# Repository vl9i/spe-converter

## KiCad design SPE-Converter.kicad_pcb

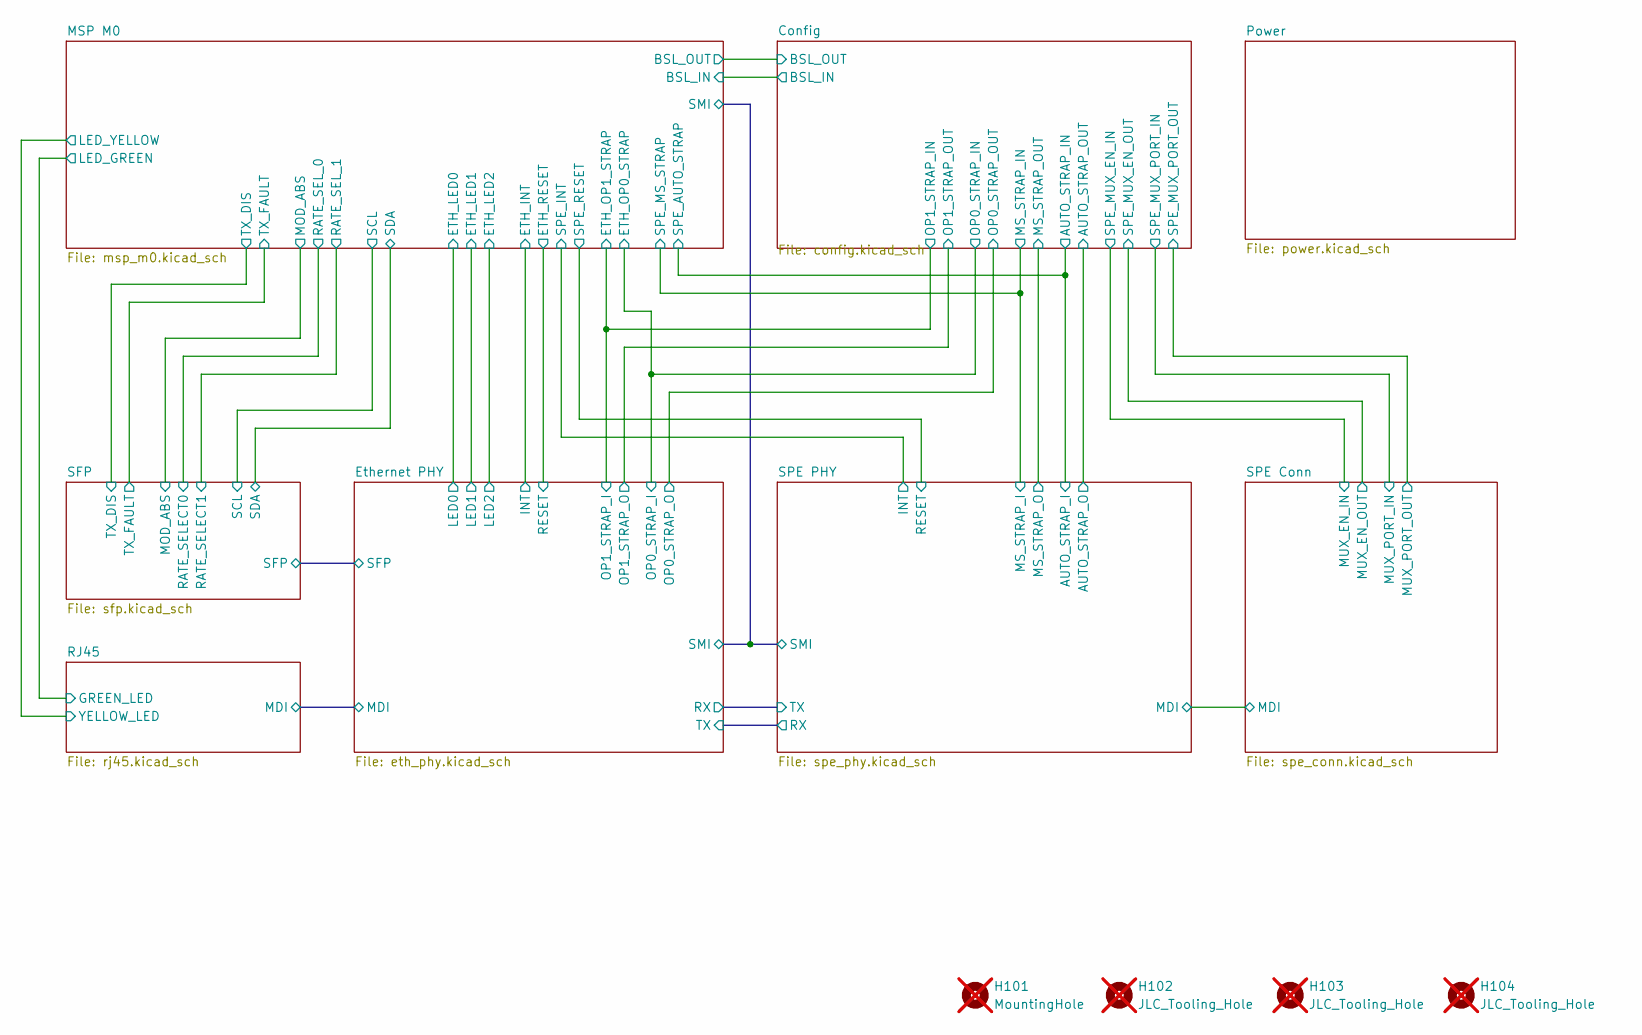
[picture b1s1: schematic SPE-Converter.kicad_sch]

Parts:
H101: MountingHole; MountingHole_2.7mm_M2.5; not fitted
H102, H103, H104: JLC_Tooling_Hole; not fitted

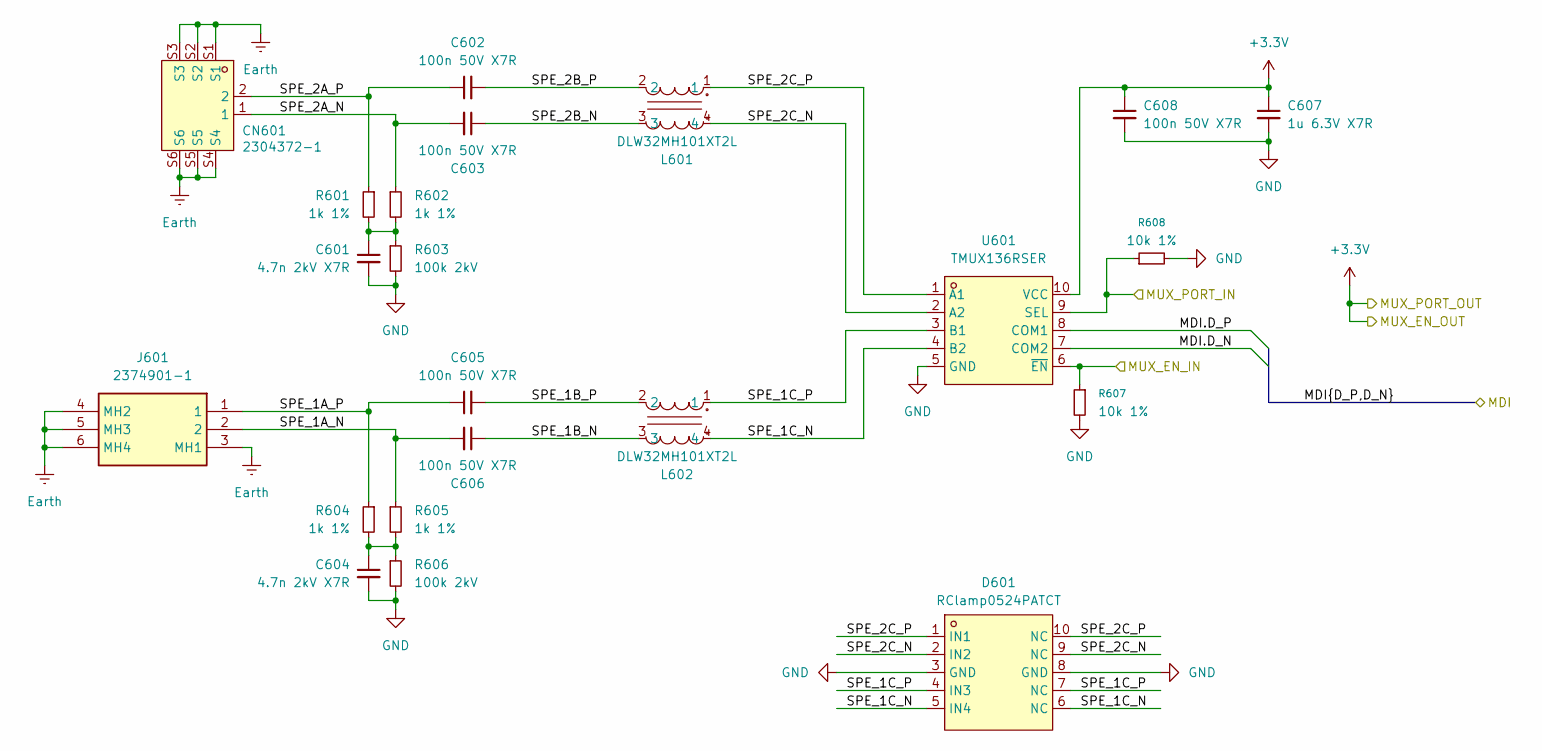
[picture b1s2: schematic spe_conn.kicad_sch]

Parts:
C601, C604: 4.7n 2kV X7R; C_1206_3216Metric
C602, C603, C605, C606, C608: 100n 50V X7R; C_0402_1005Metric
C607: 1u 6.3V X7R; C_0402_1005Metric
CN601: 2304372-1; CONN-TH_2304372-1; MPN 2304372-1; LCSC Part C5157090
D601: RClamp0524PATCT; SLP2510P8_L2.5-W1.0-P0.50-BL; MPN RClAMP0524PATCT; LCSC Part C40960
J601: 2374901-1; 23749011; Mouser Part Number 571-2374901-1
L601, L602: DLW32MH101XT2L; FILTER-SMD_4P-L3.2-W2.5-BL_DLW32SH510XK2L; LCSC Part C2935101
R601, R602, R604, R605: 1k 1%; R_0805_2012Metric
R603, R606: 100k 2kV; R_1206_3216Metric
R607, R608: 10k 1%; R_0402_1005Metric
U601: TMUX136RSER; UQFN-10_L2.0-W1.5-P0.50-TL; MPN TMUX136RSER; LCSC Part C2673272

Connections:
+3.3V: C607.1, C608.1, U601.10 (VCC); also elsewhere on the board
/Config/SPE_MUX_EN_IN: R607.1, U601.6 (~EN); also elsewhere on the board
/Config/SPE_MUX_PORT_IN: R608.1, U601.9 (SEL); also elsewhere on the board
/SPE Conn/MDI.D_N: U601.7 (COM2); also elsewhere on the board
/SPE Conn/MDI.D_P: U601.8 (COM1); also elsewhere on the board
/SPE Conn/SPE_1A_N: C606.2, J601.2, R605.1
/SPE Conn/SPE_1A_P: C605.1, J601.1, R604.1
/SPE Conn/SPE_1B_N: C606.1, L602.3
/SPE Conn/SPE_1B_P: C605.2, L602.2
/SPE Conn/SPE_1C_N: D601.5 (IN4), D601.6 (NC), L602.4, U601.4 (B2)
/SPE Conn/SPE_1C_P: D601.4 (IN3), D601.7 (NC), L602.1, U601.3 (B1)
/SPE Conn/SPE_2A_N: C603.2, CN601.1, R602.1
/SPE Conn/SPE_2A_P: C602.1, CN601.2, R601.1
/SPE Conn/SPE_2B_N: C603.1, L601.3
/SPE Conn/SPE_2B_P: C602.2, L601.2
/SPE Conn/SPE_2C_N: D601.2 (IN2), D601.9 (NC), L601.4, U601.2 (A2)
/SPE Conn/SPE_2C_P: D601.1 (IN1), D601.10 (NC), L601.1, U601.1 (A1)
Earth: CN601.S1, CN601.S2, CN601.S3, CN601.S4, CN601.S5, CN601.S6, J601.3 (MH1), J601.4 (MH2), J601.5 (MH3), J601.6 (MH4); also elsewhere on the board
GND: C601.2, C604.2, C607.2, C608.2, D601.3 (GND), D601.8 (GND), R603.2, R606.2, R607.2, R608.2, U601.5 (GND); also elsewhere on the board
unnamed: C601.1, R601.2, R602.2, R603.1
unnamed: C604.1, R604.2, R605.2, R606.1

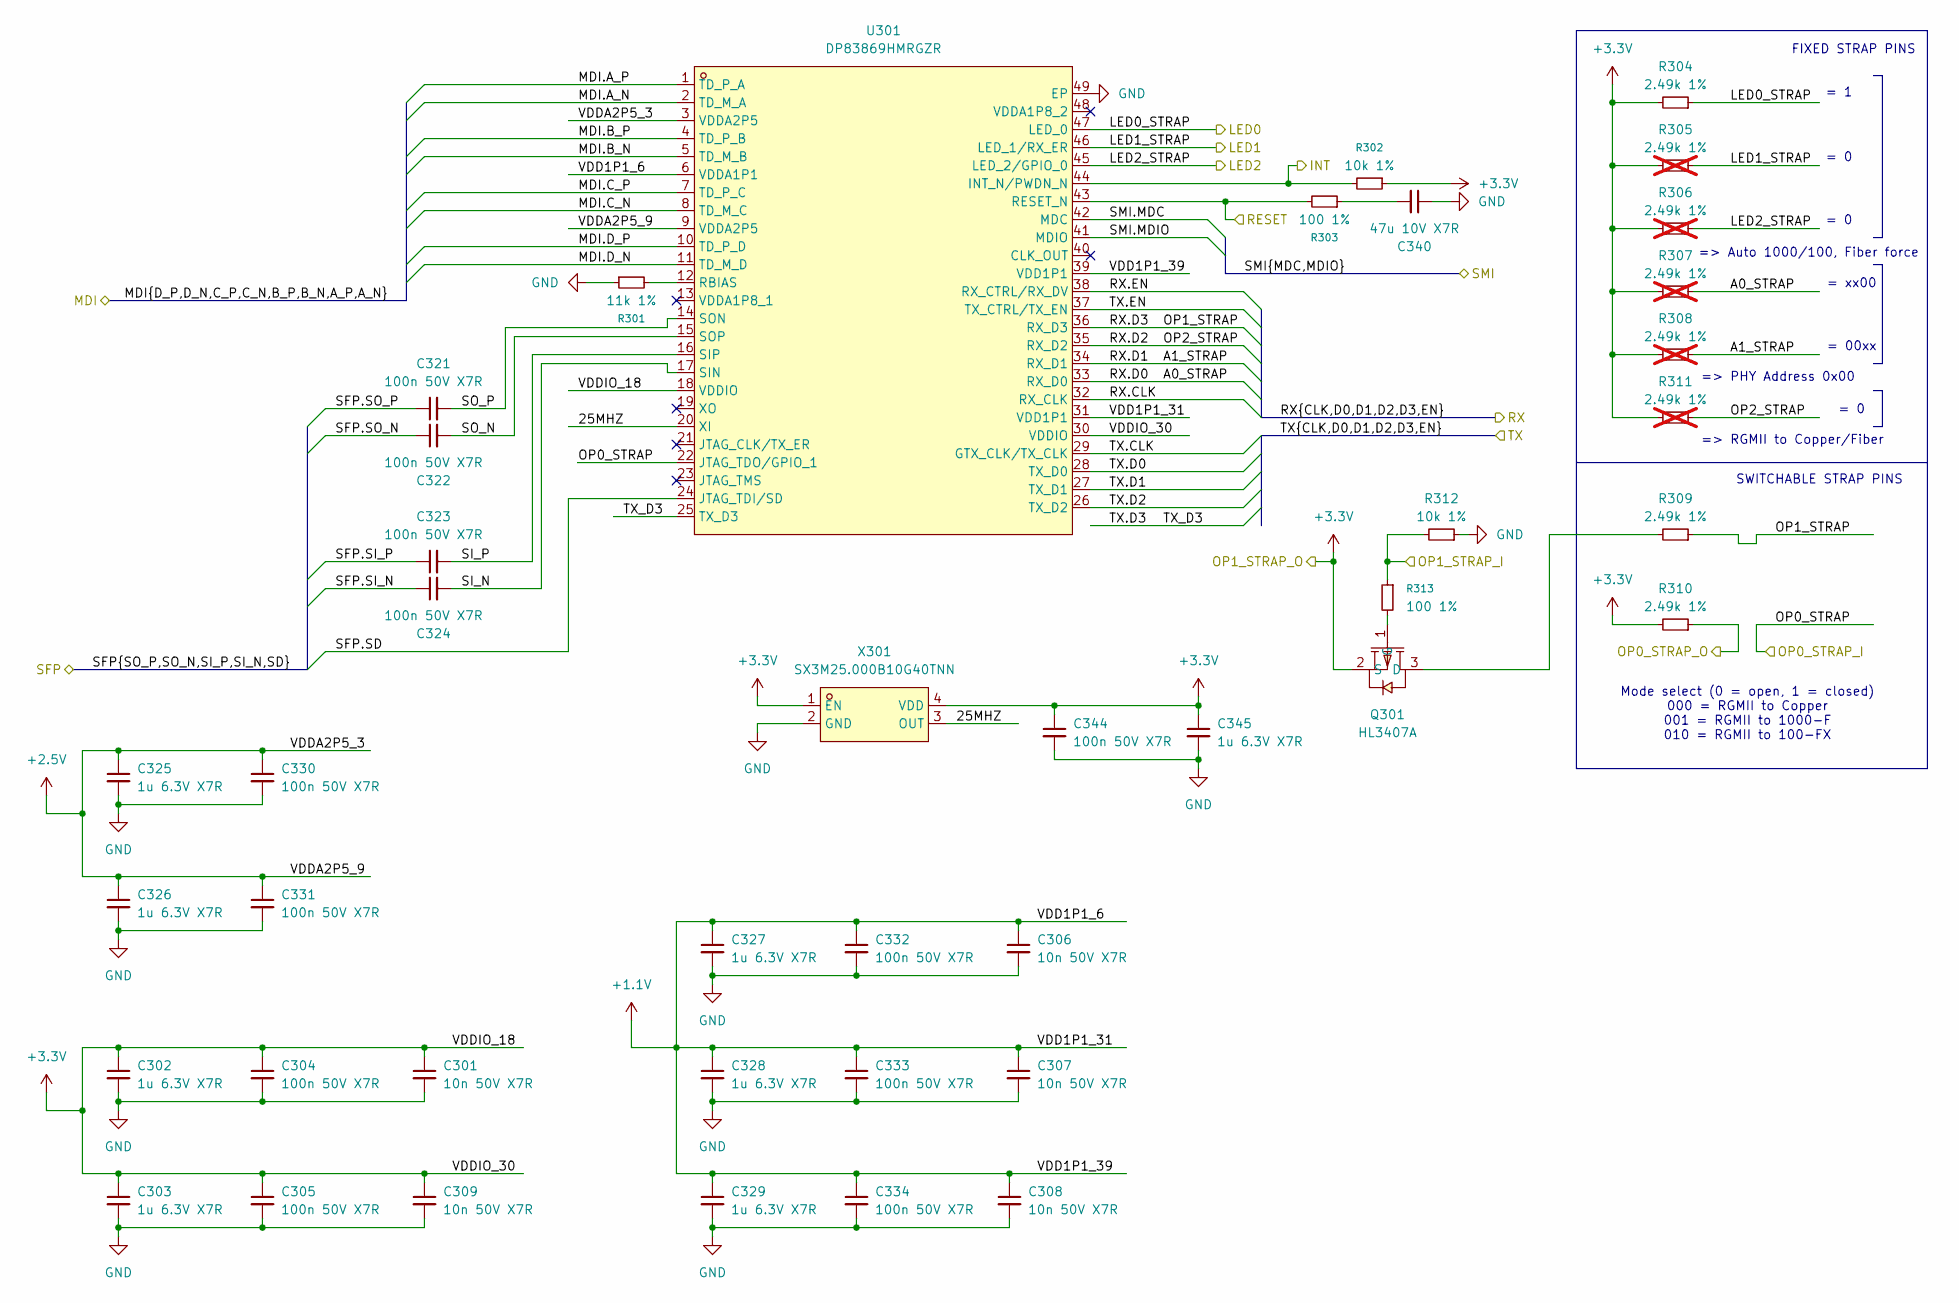
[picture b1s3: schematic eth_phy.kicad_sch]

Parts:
C301, C306, C307, C308, C309: 10n 50V X7R; C_0402_1005Metric
C302, C303, C325, C326, C327, C328, C329, C345: 1u 6.3V X7R; C_0402_1005Metric
C304, C305, C321, C322, C323, C324, C330, C331, C332, C333, C334, C344: 100n 50V X7R; C_0402_1005Metric
C340: 47u 10V X7R; C_1206_3216Metric
Q301: HL3407A; SOT-23-3_L2.9-W1.3-P1.90-LS2.4-BL-1; MPN HL3407A; LCSC Part C28646269
R301: 11k 1%; R_0402_1005Metric
R302, R312: 10k 1%; R_0402_1005Metric
R303, R313: 100 1%; R_0402_1005Metric
R304, R309, R310: 2.49k 1%; R_0402_1005Metric
R305, R306, R307, R308, R311: 2.49k 1%; R_0402_1005Metric; not fitted
U301: DP83869HMRGZR; VQFN-48_L7.0-W7.0-P0.50-TL-EP; LCSC Part C2672408
X301: SX3M25.000B10G40TNN; OSC-SMD_4P-L3.2-W2.5-BL-1; MPN SX3M25.000B10G40TNN; LCSC Part C5452698

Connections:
+1.1V: C306.1, C307.1, C308.1, C327.1, C328.1, C329.1, C332.1, C333.1, C334.1, U301.6 (VDDA1P1), U301.31 (VDD1P1), U301.39 (VDD1P1); also elsewhere on the board
+2.5V: C325.1, C326.1, C330.1, C331.1, U301.3 (VDDA2P5), U301.9 (VDDA2P5); also elsewhere on the board
+3.3V: C301.1, C302.1, C303.1, C304.1, C305.1, C309.1, C344.1, C345.1, Q301.2 (S), R302.1, R304.2, R305.2, R306.2, R307.2, R308.2, R310.2, R311.2, U301.18 (VDDIO), U301.30 (VDDIO), X301.1 (EN), X301.4 (VDD); also elsewhere on the board
/Config/OP0_STRAP_OUT: R310.1; also elsewhere on the board
/Config/OP1_STRAP_IN: R312.2, R313.1; also elsewhere on the board
/Ethernet PHY/25MHZ: U301.20 (XI), X301.3 (OUT)
/Ethernet PHY/INT: R302.2, U301.44 (INT_N/PWDN_N); also elsewhere on the board
/Ethernet PHY/LED0_STRAP: R304.1, U301.47 (LED_0); also elsewhere on the board
/Ethernet PHY/LED1_STRAP: R305.1, U301.46 (LED_1/RX_ER); also elsewhere on the board
/Ethernet PHY/LED2_STRAP: R306.1, U301.45 (LED_2/GPIO_0); also elsewhere on the board
/Ethernet PHY/MDI.A_N: U301.2 (TD_M_A); also elsewhere on the board
/Ethernet PHY/MDI.A_P: U301.1 (TD_P_A); also elsewhere on the board
/Ethernet PHY/MDI.B_N: U301.5 (TD_M_B); also elsewhere on the board
/Ethernet PHY/MDI.B_P: U301.4 (TD_P_B); also elsewhere on the board
/Ethernet PHY/MDI.C_N: U301.8 (TD_M_C); also elsewhere on the board
/Ethernet PHY/MDI.C_P: U301.7 (TD_P_C); also elsewhere on the board
/Ethernet PHY/MDI.D_N: U301.11 (TD_M_D); also elsewhere on the board
/Ethernet PHY/MDI.D_P: U301.10 (TD_P_D); also elsewhere on the board
/Ethernet PHY/OP0_STRAP: U301.22 (JTAG_TDO/GPIO_1); also elsewhere on the board
/Ethernet PHY/RESET: R303.2, U301.43 (RESET_N); also elsewhere on the board
/Ethernet PHY/RX.CLK: U301.32 (RX_CLK); also elsewhere on the board
/Ethernet PHY/RX.D0: R307.1, U301.33 (RX_D0); also elsewhere on the board
/Ethernet PHY/RX.D1: R308.1, U301.34 (RX_D1); also elsewhere on the board
/Ethernet PHY/RX.D2: R311.1, U301.35 (RX_D2); also elsewhere on the board
/Ethernet PHY/RX.D3: R309.1, U301.36 (RX_D3); also elsewhere on the board
/Ethernet PHY/RX.EN: U301.38 (RX_CTRL/RX_DV); also elsewhere on the board
/Ethernet PHY/SFP.SD: U301.24 (JTAG_TDI/SD); also elsewhere on the board
/Ethernet PHY/SFP.SI_N: C324.1; also elsewhere on the board
/Ethernet PHY/SFP.SI_P: C323.1; also elsewhere on the board
/Ethernet PHY/SFP.SO_N: C322.1; also elsewhere on the board
/Ethernet PHY/SFP.SO_P: C321.1; also elsewhere on the board
/Ethernet PHY/SI_N: C324.2, U301.17 (SIN)
/Ethernet PHY/SI_P: C323.2, U301.16 (SIP)
/Ethernet PHY/SMI.MDC: U301.42 (MDC); also elsewhere on the board
/Ethernet PHY/SMI.MDIO: U301.41 (MDIO); also elsewhere on the board
/Ethernet PHY/SO_N: C322.2, U301.15 (SOP)
/Ethernet PHY/SO_P: C321.2, U301.14 (SON)
/Ethernet PHY/TX.CLK: U301.29 (GTX_CLK/TX_CLK); also elsewhere on the board
/Ethernet PHY/TX.D0: U301.28 (TX_D0); also elsewhere on the board
/Ethernet PHY/TX.D1: U301.27 (TX_D1); also elsewhere on the board
/Ethernet PHY/TX.D2: U301.26 (TX_D2); also elsewhere on the board
/Ethernet PHY/TX.D3: U301.25 (TX_D3); also elsewhere on the board
/Ethernet PHY/TX.EN: U301.37 (TX_CTRL/TX_EN); also elsewhere on the board
GND: C301.2, C302.2, C303.2, C304.2, C305.2, C306.2, C307.2, C308.2, C309.2, C325.2, C326.2, C327.2, C328.2, C329.2, C330.2, C331.2, C332.2, C333.2, C334.2, C340.1, C344.2, C345.2, R301.1, R312.1, U301.49 (EP), X301.2 (GND); also elsewhere on the board
unnamed: C340.2, R303.1
unnamed: Q301.3 (D), R309.2
unnamed: Q301.1 (G), R313.2
unnamed: R301.2, U301.12 (RBIAS)

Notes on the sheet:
Mode select (0 = open, 1 = closed) 000 = RGMII to Copper 001 = RGMII to 1000-F 010 = RGMII to 100-FX
=> RGMII to Copper/Fiber
= 0
=> Auto 1000/100, Fiber force
= xx00
FIXED STRAP PINS
= 0
= 00xx
=> PHY Address 0x00
SWITCHABLE STRAP PINS
= 1

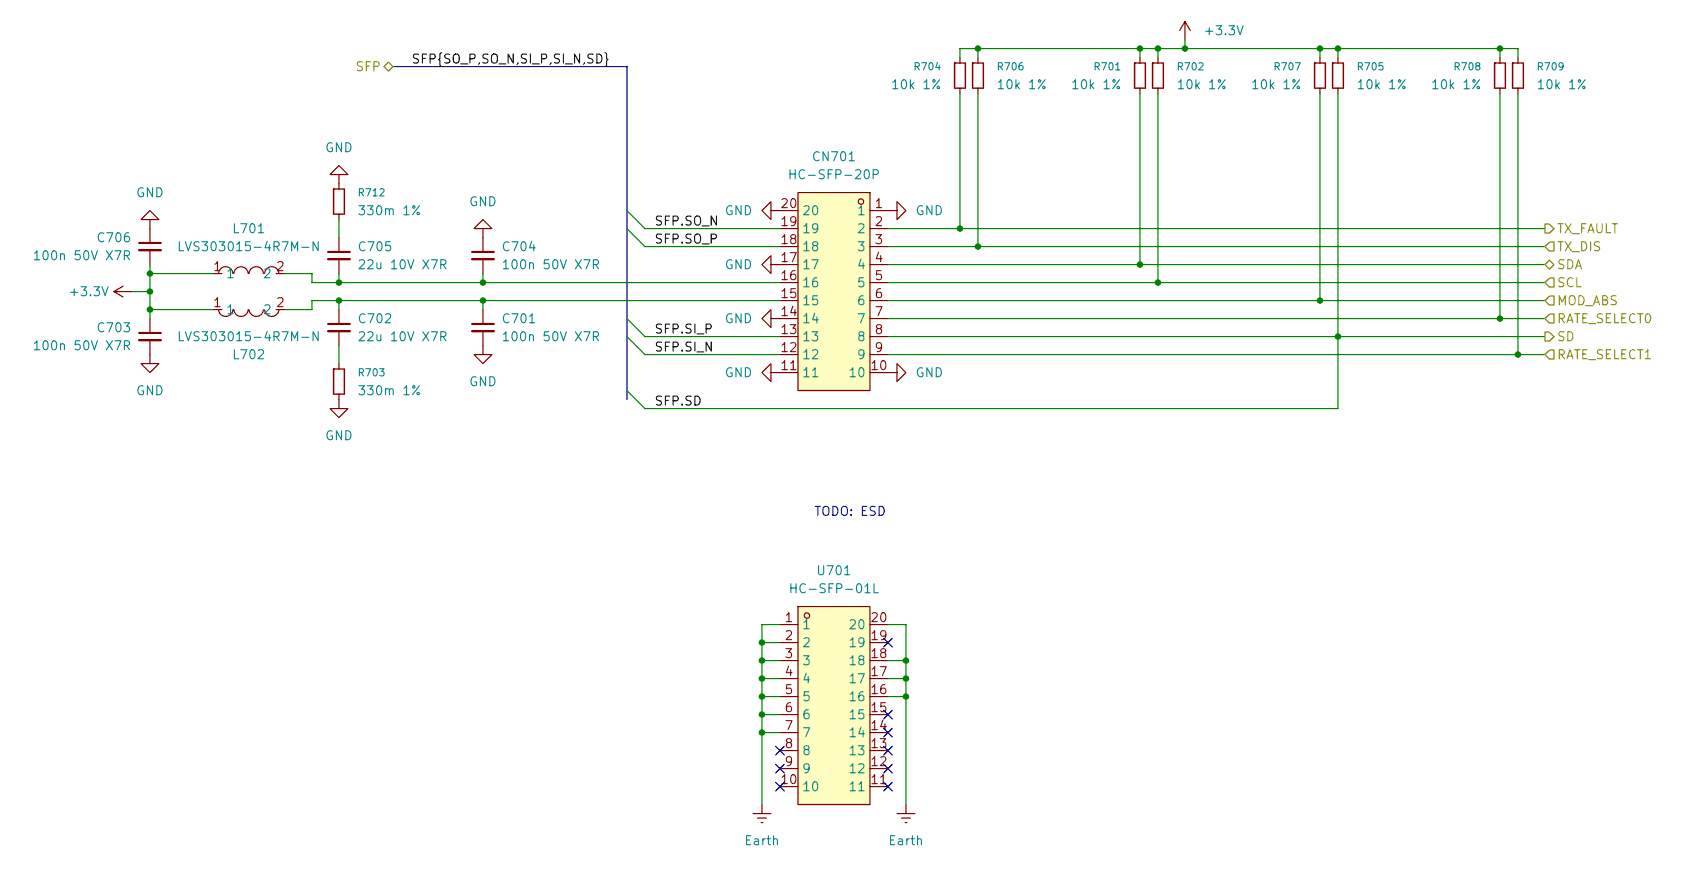
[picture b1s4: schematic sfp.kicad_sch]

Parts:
C701, C703, C704, C706: 100n 50V X7R; C_0402_1005Metric
C702, C705: 22u 10V X7R; C_0805_2012Metric
CN701: HC-SFP-20P; CONN-SMD_20P-P0.80_HCTL_HC-SFP-20P; MPN HC-SFP-20P; LCSC Part C2897291
L701, L702: LVS303015-4R7M-N; IND-SMD_L3.0-W3.0_NR3010; MPN LVS303015-4R7M-N; LCSC Part C280523
R701, R702, R704, R705, R706, R707, R708, R709: 10k 1%; R_0402_1005Metric
R703, R712: 330m 1%; R_0402_1005Metric
U701: HC-SFP-01L; TH_HC-SFP-01L; MPN HC-SFP-01L; LCSC Part C2897292

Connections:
+3.3V: C703.1, C706.2, L701.1, L702.1, R701.1, R702.1, R704.1, R705.1, R706.1, R707.1, R708.1, R709.1; also elsewhere on the board
/Ethernet PHY/SFP.SD: CN701.8, R705.2; also elsewhere on the board
/Ethernet PHY/SFP.SI_N: CN701.12; also elsewhere on the board
/Ethernet PHY/SFP.SI_P: CN701.13; also elsewhere on the board
/Ethernet PHY/SFP.SO_N: CN701.19; also elsewhere on the board
/Ethernet PHY/SFP.SO_P: CN701.18; also elsewhere on the board
/MSP M0/MOD_ABS: CN701.6, R707.2; also elsewhere on the board
/MSP M0/RATE_SEL_0: CN701.7, R708.2; also elsewhere on the board
/MSP M0/RATE_SEL_1: CN701.9, R709.2; also elsewhere on the board
/MSP M0/SCL: CN701.5, R702.2; also elsewhere on the board
/MSP M0/SDA: CN701.4, R701.2; also elsewhere on the board
/MSP M0/TX_DIS: CN701.3, R706.2; also elsewhere on the board
/MSP M0/TX_FAULT: CN701.2, R704.2; also elsewhere on the board
Earth: U701.1, U701.2, U701.3, U701.4, U701.5, U701.6, U701.7, U701.16, U701.17, U701.18, U701.20; also elsewhere on the board
GND: C701.2, C703.2, C704.1, C706.1, CN701.1, CN701.10, CN701.11, CN701.14, CN701.17, CN701.20, R703.2, R712.1; also elsewhere on the board
unnamed: C701.1, C702.1, CN701.15, L702.2
unnamed: C702.2, R703.1
unnamed: C704.2, C705.2, CN701.16, L701.2
unnamed: C705.1, R712.2

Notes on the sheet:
TODO: ESD

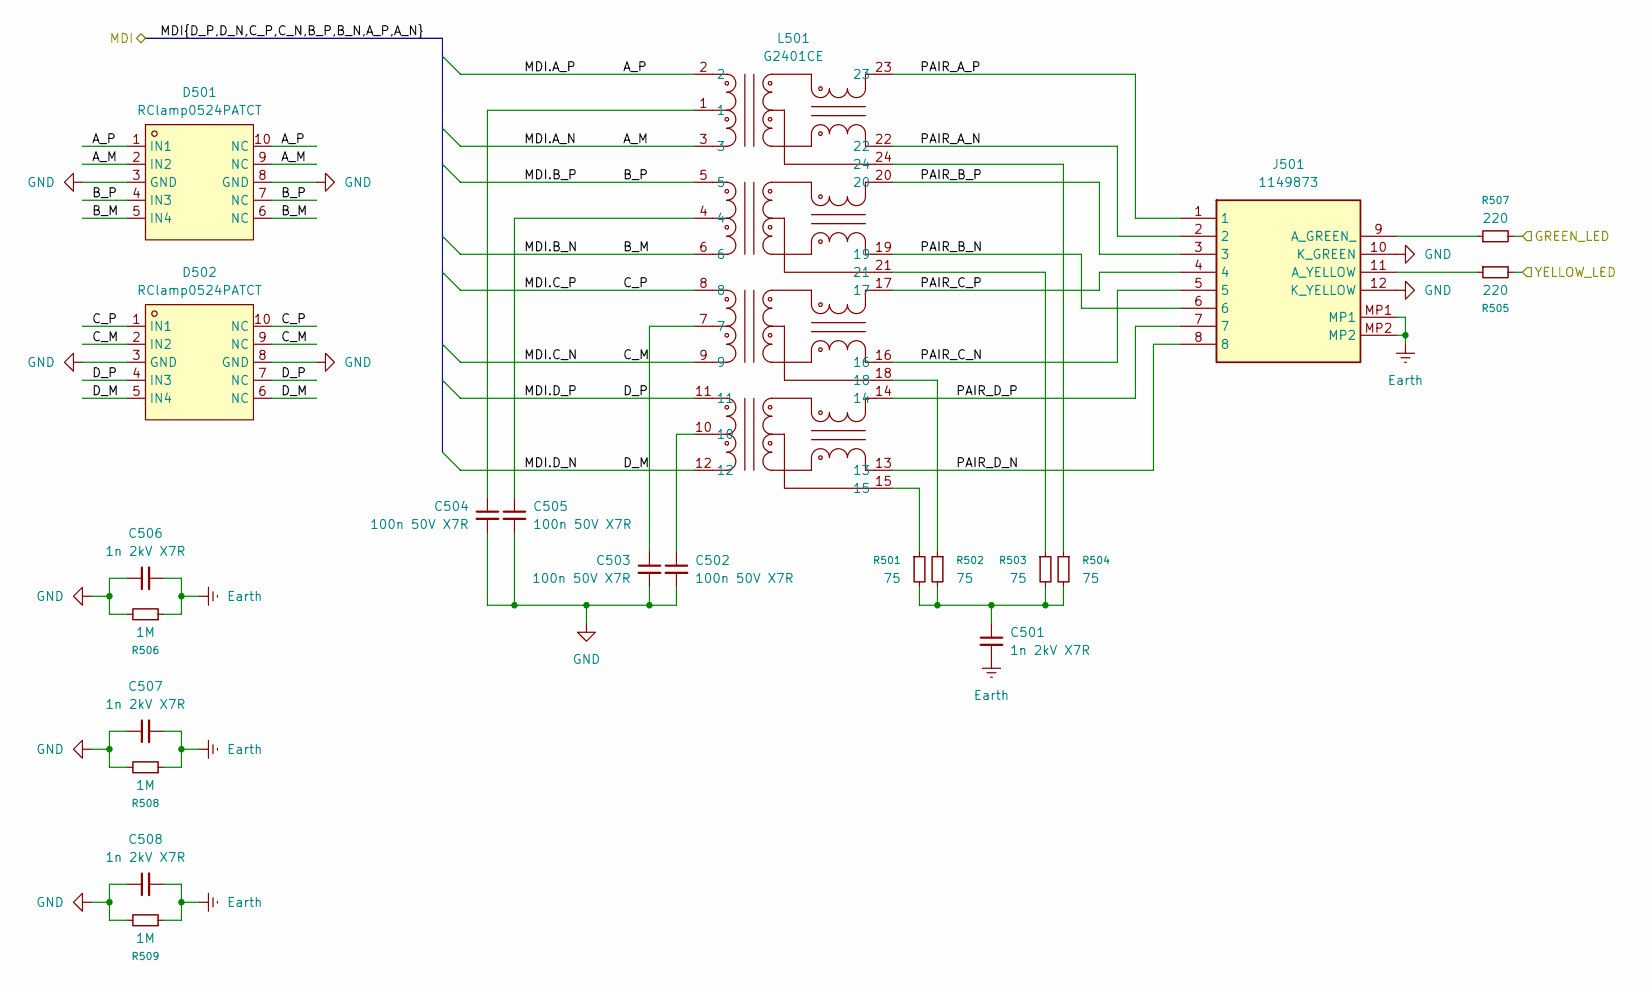
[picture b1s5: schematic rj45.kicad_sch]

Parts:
C501, C506, C507, C508: 1n 2kV X7R; C_1210_3225Metric
C502, C503, C504, C505: 100n 50V X7R; C_0402_1005Metric
D501, D502: RClamp0524PATCT; SLP2510P8_L2.5-W1.0-P0.50-BL; MPN RClAMP0524PATCT; LCSC Part C40960
J501: 1149873; Manufacturer_Part_Number 1149873; Mouser Part Number 651-1149873
L501: G2401CE; SMD-24_L15.1-W7.1-P1.00-LS10.0-BL; MPN G2401CE; LCSC Part C2904710
R501, R502, R503, R504: 75; R_0402_1005Metric
R505, R507: 220; R_0402_1005Metric
R506, R508, R509: 1M; R_1206_3216Metric

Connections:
/Ethernet PHY/MDI.A_N: D501.2 (IN2), D501.9 (NC), L501.3; also elsewhere on the board
/Ethernet PHY/MDI.A_P: D501.1 (IN1), D501.10 (NC), L501.2; also elsewhere on the board
/Ethernet PHY/MDI.B_N: D501.5 (IN4), D501.6 (NC), L501.6; also elsewhere on the board
/Ethernet PHY/MDI.B_P: D501.4 (IN3), D501.7 (NC), L501.5; also elsewhere on the board
/Ethernet PHY/MDI.C_N: D502.2 (IN2), D502.9 (NC), L501.9; also elsewhere on the board
/Ethernet PHY/MDI.C_P: D502.1 (IN1), D502.10 (NC), L501.8; also elsewhere on the board
/Ethernet PHY/MDI.D_N: D502.5 (IN4), D502.6 (NC), L501.12; also elsewhere on the board
/Ethernet PHY/MDI.D_P: D502.4 (IN3), D502.7 (NC), L501.11; also elsewhere on the board
/MSP M0/LED_GREEN: R507.2; also elsewhere on the board
/MSP M0/LED_YELLOW: R505.2; also elsewhere on the board
/RJ45/PAIR_A_N: J501.2, L501.22
/RJ45/PAIR_A_P: J501.1, L501.23
/RJ45/PAIR_B_N: J501.6, L501.19
/RJ45/PAIR_B_P: J501.3, L501.20
/RJ45/PAIR_C_N: J501.5, L501.16
/RJ45/PAIR_C_P: J501.4, L501.17
/RJ45/PAIR_D_N: J501.8, L501.13
/RJ45/PAIR_D_P: J501.7, L501.14
Earth: C501.2, C506.2, C507.2, C508.2, J501.MP1, J501.MP2, R506.1, R508.1, R509.1; also elsewhere on the board
GND: C502.2, C503.2, C504.2, C505.2, C506.1, C507.1, C508.1, D501.3 (GND), D501.8 (GND), D502.3 (GND), D502.8 (GND), J501.10 (K_GREEN), J501.12 (K_YELLOW), R506.2, R508.2, R509.2; also elsewhere on the board
unnamed: C501.1, R501.2, R502.2, R503.2, R504.2
unnamed: C502.1, L501.10
unnamed: C503.1, L501.7
unnamed: C504.1, L501.1
unnamed: C505.1, L501.4
unnamed: J501.9 (A_GREEN_), R507.1
unnamed: J501.11 (A_YELLOW), R505.1
unnamed: L501.15, R501.1
unnamed: L501.18, R502.1
unnamed: L501.21, R503.1
unnamed: L501.24, R504.1

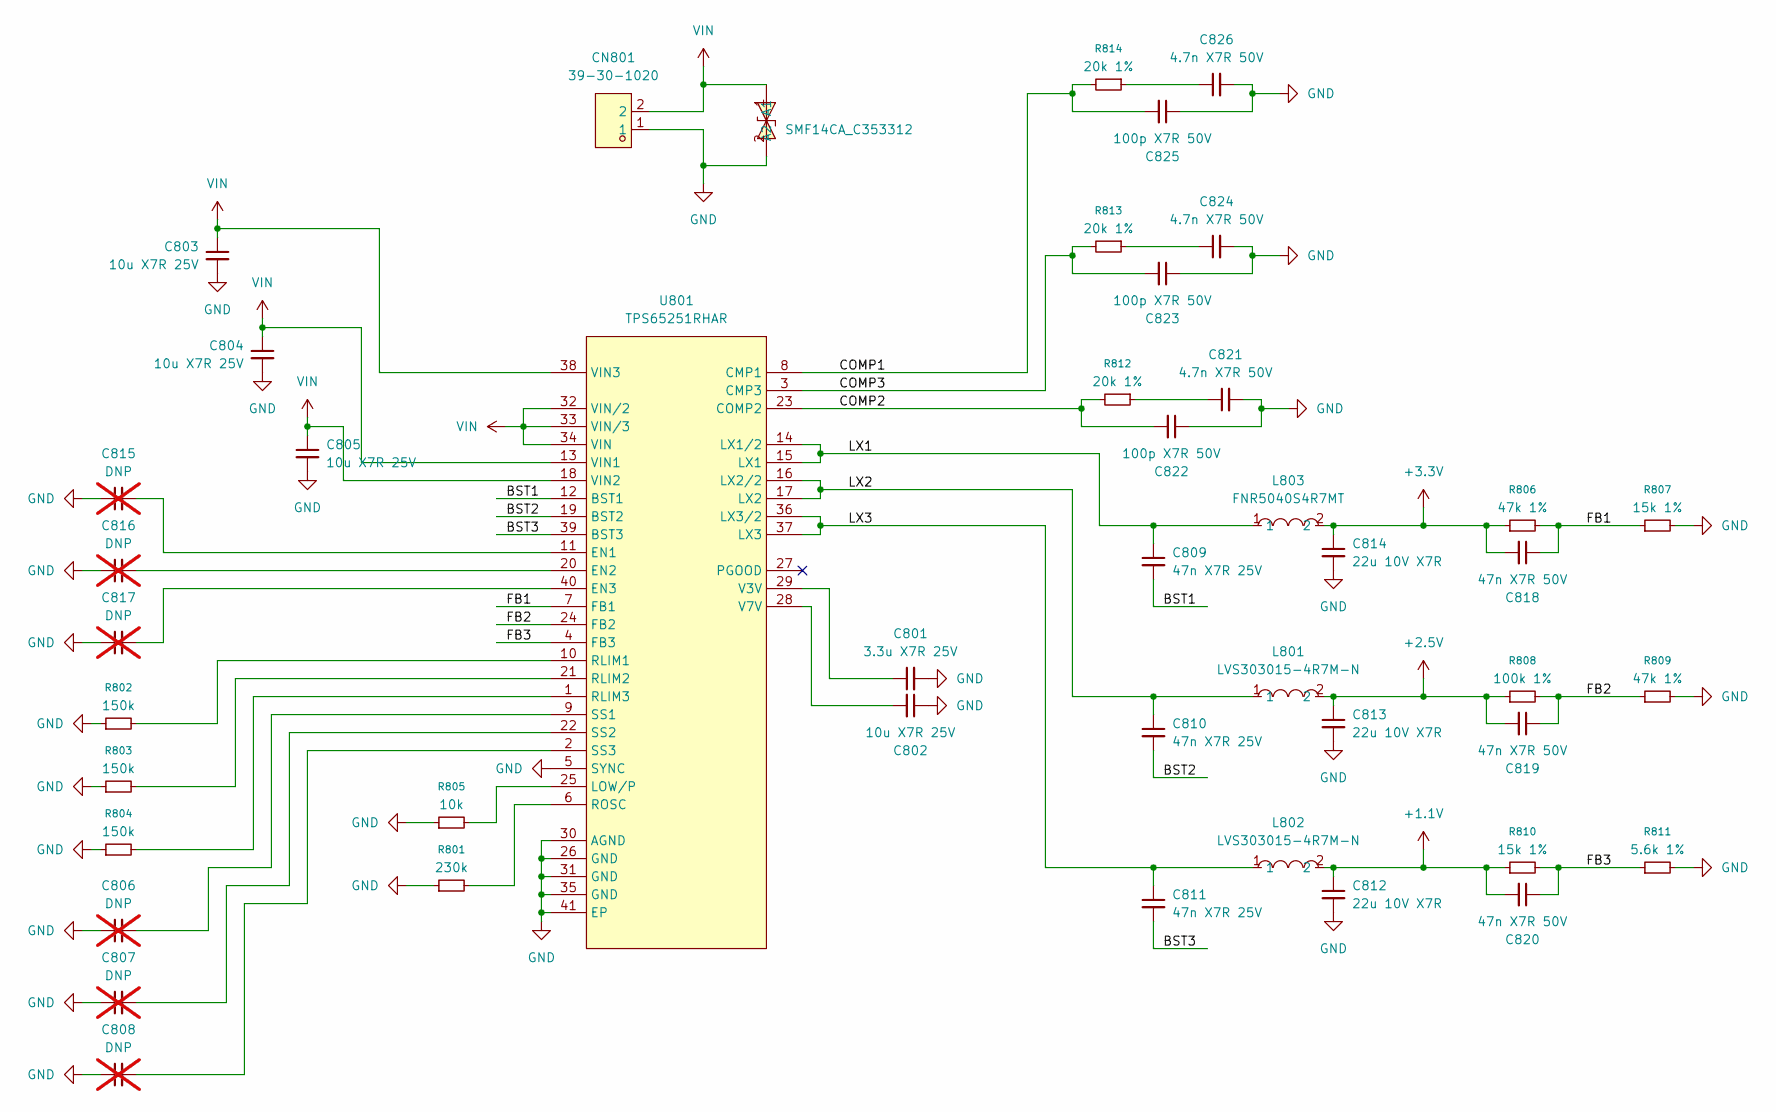
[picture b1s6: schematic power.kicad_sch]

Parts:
C801: 3.3u X7R 25V; C_0805_2012Metric
C802, C803, C804, C805: 10u X7R 25V; C_0805_2012Metric
C806, C807, C808, C815, C816, C817: DNP; C_0402_1005Metric; not fitted
C809, C810, C811: 47n X7R 25V; C_0402_1005Metric
C812, C813, C814: 22u 10V X7R; C_0805_2012Metric
C818, C819, C820: 47n X7R 50V; C_0402_1005Metric
C821, C824, C826: 4.7n X7R 50V; C_0402_1005Metric
C822, C823, C825: 100p X7R 50V; C_0402_1005Metric
CN801: 39-30-1020; CONN-TH_2P-P5.50_39-30-1020; MPN 39301020; LCSC Part C240832
D801: SMF14CA_C353312; SOD-123FL_L2.8-W1.8-LS3.7-BI; MPN SMF14CA; LCSC Part C353312
L801, L802: LVS303015-4R7M-N; IND-SMD_L3.0-W3.0_NR3010; MPN LVS303015-4R7M-N; LCSC Part C280523
L803: FNR5040S4R7MT; IND-SMD_L5.0-W5.0_FNR50XXS; MPN FNR5040S4R7MT; LCSC Part C167963
R801: 230k; R_0402_1005Metric
R802, R803, R804: 150k; R_0402_1005Metric
R805: 10k; R_0402_1005Metric
R806, R809: 47k 1%; R_0402_1005Metric
R807, R810: 15k 1%; R_0402_1005Metric
R808: 100k 1%; R_0402_1005Metric
R811: 5.6k 1%; R_0402_1005Metric
R812, R813, R814: 20k 1%; R_0402_1005Metric
U801: TPS65251RHAR; VQFN-40_L6.0-W6.0-P0.50-TL-EP; MPN TPS65251RHAR; LCSC Part C60246

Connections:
+1.1V: C812.1, C820.2, L802.2, R810.1; also elsewhere on the board
+2.5V: C813.1, C819.2, L801.2, R808.1; also elsewhere on the board
+3.3V: C814.1, C818.2, L803.2, R806.1; also elsewhere on the board
/Power/BST1: C809.2, U801.12 (BST1)
/Power/BST2: C810.2, U801.19 (BST2)
/Power/BST3: C811.2, U801.39 (BST3)
/Power/COMP1: C825.2, R814.2, U801.8 (CMP1)
/Power/COMP2: C822.2, R812.2, U801.23 (COMP2)
/Power/COMP3: C823.2, R813.2, U801.3 (CMP3)
/Power/FB1: C818.1, R806.2, R807.1, U801.7 (FB1)
/Power/FB2: C819.1, R808.2, R809.1, U801.24 (FB2)
/Power/FB3: C820.1, R810.2, R811.1, U801.4 (FB3)
/Power/LX1: C809.1, L803.1, U801.14 (LX1/2), U801.15 (LX1)
/Power/LX2: C810.1, L801.1, U801.16 (LX2/2), U801.17 (LX2)
/Power/LX3: C811.1, L802.1, U801.36 (LX3/2), U801.37 (LX3)
GND: C801.2, C802.1, C803.2, C804.2, C805.2, C806.1, C807.1, C808.1, C812.2, C813.2, C814.2, C815.1, C816.1, C817.1, C821.2, C822.1, C823.1, C824.2, C825.1, C826.2, CN801.1, D801.2 (A1), R801.1, R802.1, R803.1, R804.1, R805.1, R807.2, R809.2, R811.2, U801.5 (SYNC), U801.26 (GND), U801.30 (AGND), U801.31 (GND), U801.35 (GND), U801.41 (EP); also elsewhere on the board
unnamed: C821.1, R812.1
unnamed: C824.1, R813.1
unnamed: C826.1, R814.1
unnamed: C815.2, U801.11 (EN1)
unnamed: C816.2, U801.20 (EN2)
unnamed: C817.2, U801.40 (EN3)
unnamed: R805.2, U801.25 (LOW/P)
unnamed: R802.2, U801.10 (RLIM1)
unnamed: R803.2, U801.21 (RLIM2)
unnamed: R804.2, U801.1 (RLIM3)
unnamed: R801.2, U801.6 (ROSC)
unnamed: C806.2, U801.9 (SS1)
unnamed: C807.2, U801.22 (SS2)
unnamed: C808.2, U801.2 (SS3)
unnamed: C801.1, U801.29 (V3V)
unnamed: C802.2, U801.28 (V7V)
VIN: C803.1, C804.1, C805.1, CN801.2, D801.1 (A2), U801.13 (VIN1), U801.18 (VIN2), U801.32 (VIN/2), U801.33 (VIN/3), U801.34 (VIN), U801.38 (VIN3)
